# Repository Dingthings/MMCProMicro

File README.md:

# ShiroMicro
ProMicro clone with Mid-Mount USB Type-C connector

Adjusted to have same 12pin USB C connector as https://github.com/Ariamelon/Alvaro

UNTESTED

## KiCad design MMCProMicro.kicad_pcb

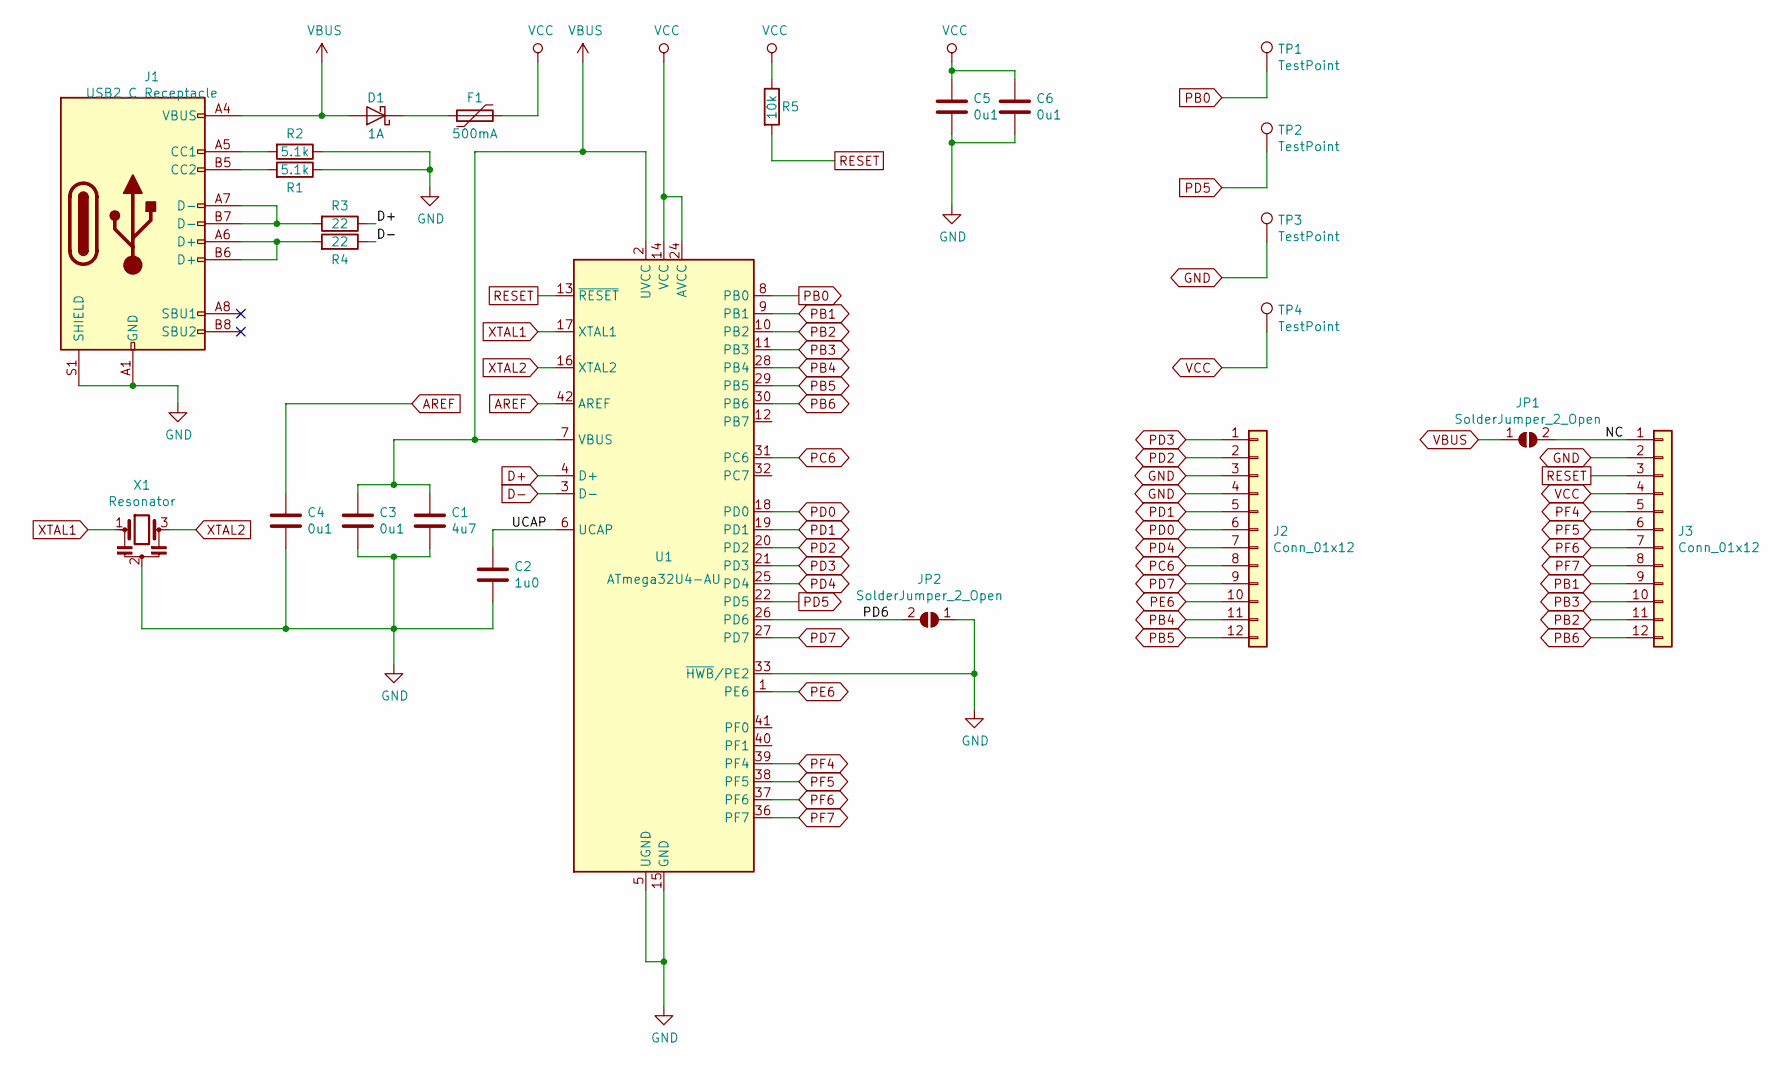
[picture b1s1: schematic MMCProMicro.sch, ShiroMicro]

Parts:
C1: 4u7; C_0603_HandSoldering
C2: 1u0; C_0603_HandSoldering
C3, C4, C5, C6: 0u1; C_0603_HandSoldering
D1: 1A; D_TUMD2_HandSoldering
F1: 500mA; F_0805_HandSoldering
J1: USB2_C_Receptacle; USB-C-C168688
J2, J3: Conn_01x12; Pin_Header_Custom_Straight_1x12_Pitch2.54mm
JP1, JP2: SolderJumper_2_Open; SolderJumper-2_P1.0mm_Open_RoundedPad0.7x1.0mm
R1, R2: 5.1k; R_0603_HandSoldering
R3, R4: 22; R_0603_HandSoldering
R5: 10k; R_0603_HandSoldering
TP1, TP2, TP3, TP4: TestPoint; Measurement_Point_RoundSquare-TH_Tiny
U1: ATmega32U4-AU; TQFP-44_10x10mm_P0.8mm
X1: Resonator; Resonator_SMD_muRata_CSTxExxV-3Pin_3.0x1.1mm_HandSoldering_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

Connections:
/NC: J3.1, JP1.2 (B)
/PD6: JP2.2 (B), U1.26 (PD6)
/UCAP: C2.1, U1.6 (UCAP)
AREF: C4.1, U1.42 (AREF)
D+: R3.1, U1.4 (D+)
D-: R4.1, U1.3 (D-)
GND: C1.2, C2.2, C3.2, C4.2, C5.2, C6.2, J1.A1 (GND), J1.A12 (GND), J1.B1 (GND), J1.B12 (GND), J1.S1 (SHIELD), J2.3, J2.4, J3.2, JP2.1 (A), R1.1, R2.1, TP3.1, U1.5 (UGND), U1.15 (GND), U1.23 (GND), U1.33 (~HWB~/PE2), U1.35 (GND), U1.43 (GND), X1.2
unnamed: D1.1 (K), F1.1
unnamed: J1.A5 (CC1), R2.2
unnamed: J1.A6 (D+), J1.B6 (D+), R4.2
unnamed: J1.A7 (D-), J1.B7 (D-), R3.2
unnamed: J1.B5 (CC2), R1.2
PB0: TP1.1, U1.8 (PB0)
PB1: J3.9, U1.9 (PB1)
PB2: J3.11, U1.10 (PB2)
PB3: J3.10, U1.11 (PB3)
PB4: J2.11, U1.28 (PB4)
PB5: J2.12, U1.29 (PB5)
PB6: J3.12, U1.30 (PB6)
PC6: J2.8, U1.31 (PC6)
PD0: J2.6, U1.18 (PD0)
PD1: J2.5, U1.19 (PD1)
PD2: J2.2, U1.20 (PD2)
PD3: J2.1, U1.21 (PD3)
PD4: J2.7, U1.25 (PD4)
PD5: TP2.1, U1.22 (PD5)
PD7: J2.9, U1.27 (PD7)
PE6: J2.10, U1.1 (PE6)
PF4: J3.5, U1.39 (PF4)
PF5: J3.6, U1.38 (PF5)
PF6: J3.7, U1.37 (PF6)
PF7: J3.8, U1.36 (PF7)
RESET: J3.3, R5.2, U1.13 (~RESET)
VBUS: C1.1, C3.1, D1.2 (A), J1.A4 (VBUS), J1.A9 (VBUS), J1.B4 (VBUS), J1.B9 (VBUS), JP1.1 (A), U1.2 (UVCC), U1.7 (VBUS)
VCC: C5.1, C6.1, F1.2, J3.4, R5.1, TP4.1, U1.14 (VCC), U1.24 (AVCC), U1.34 (VCC), U1.44 (AVCC)
XTAL1: U1.17 (XTAL1), X1.1
XTAL2: U1.16 (XTAL2), X1.3

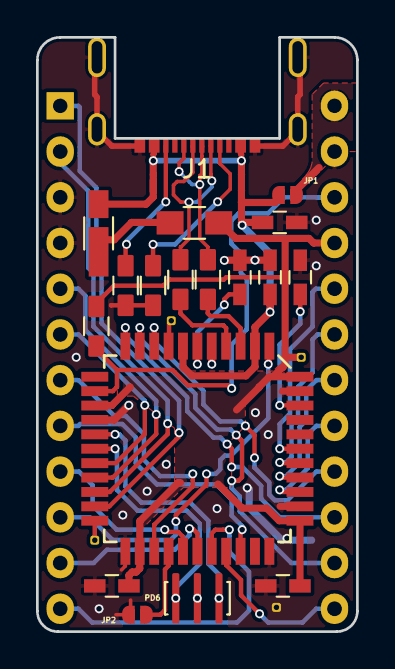
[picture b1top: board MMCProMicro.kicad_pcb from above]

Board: 2 copper layers, 17.8 x 33.0 mm, 25 parts (0 on the bottom side), 37 nets.

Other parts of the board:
Ref**: Val**; dinkyLogo

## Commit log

2020-10-10 Rerouted
2021-05-02 12p schematic + board
2021-05-02 Add files via upload
    Updated BOM
